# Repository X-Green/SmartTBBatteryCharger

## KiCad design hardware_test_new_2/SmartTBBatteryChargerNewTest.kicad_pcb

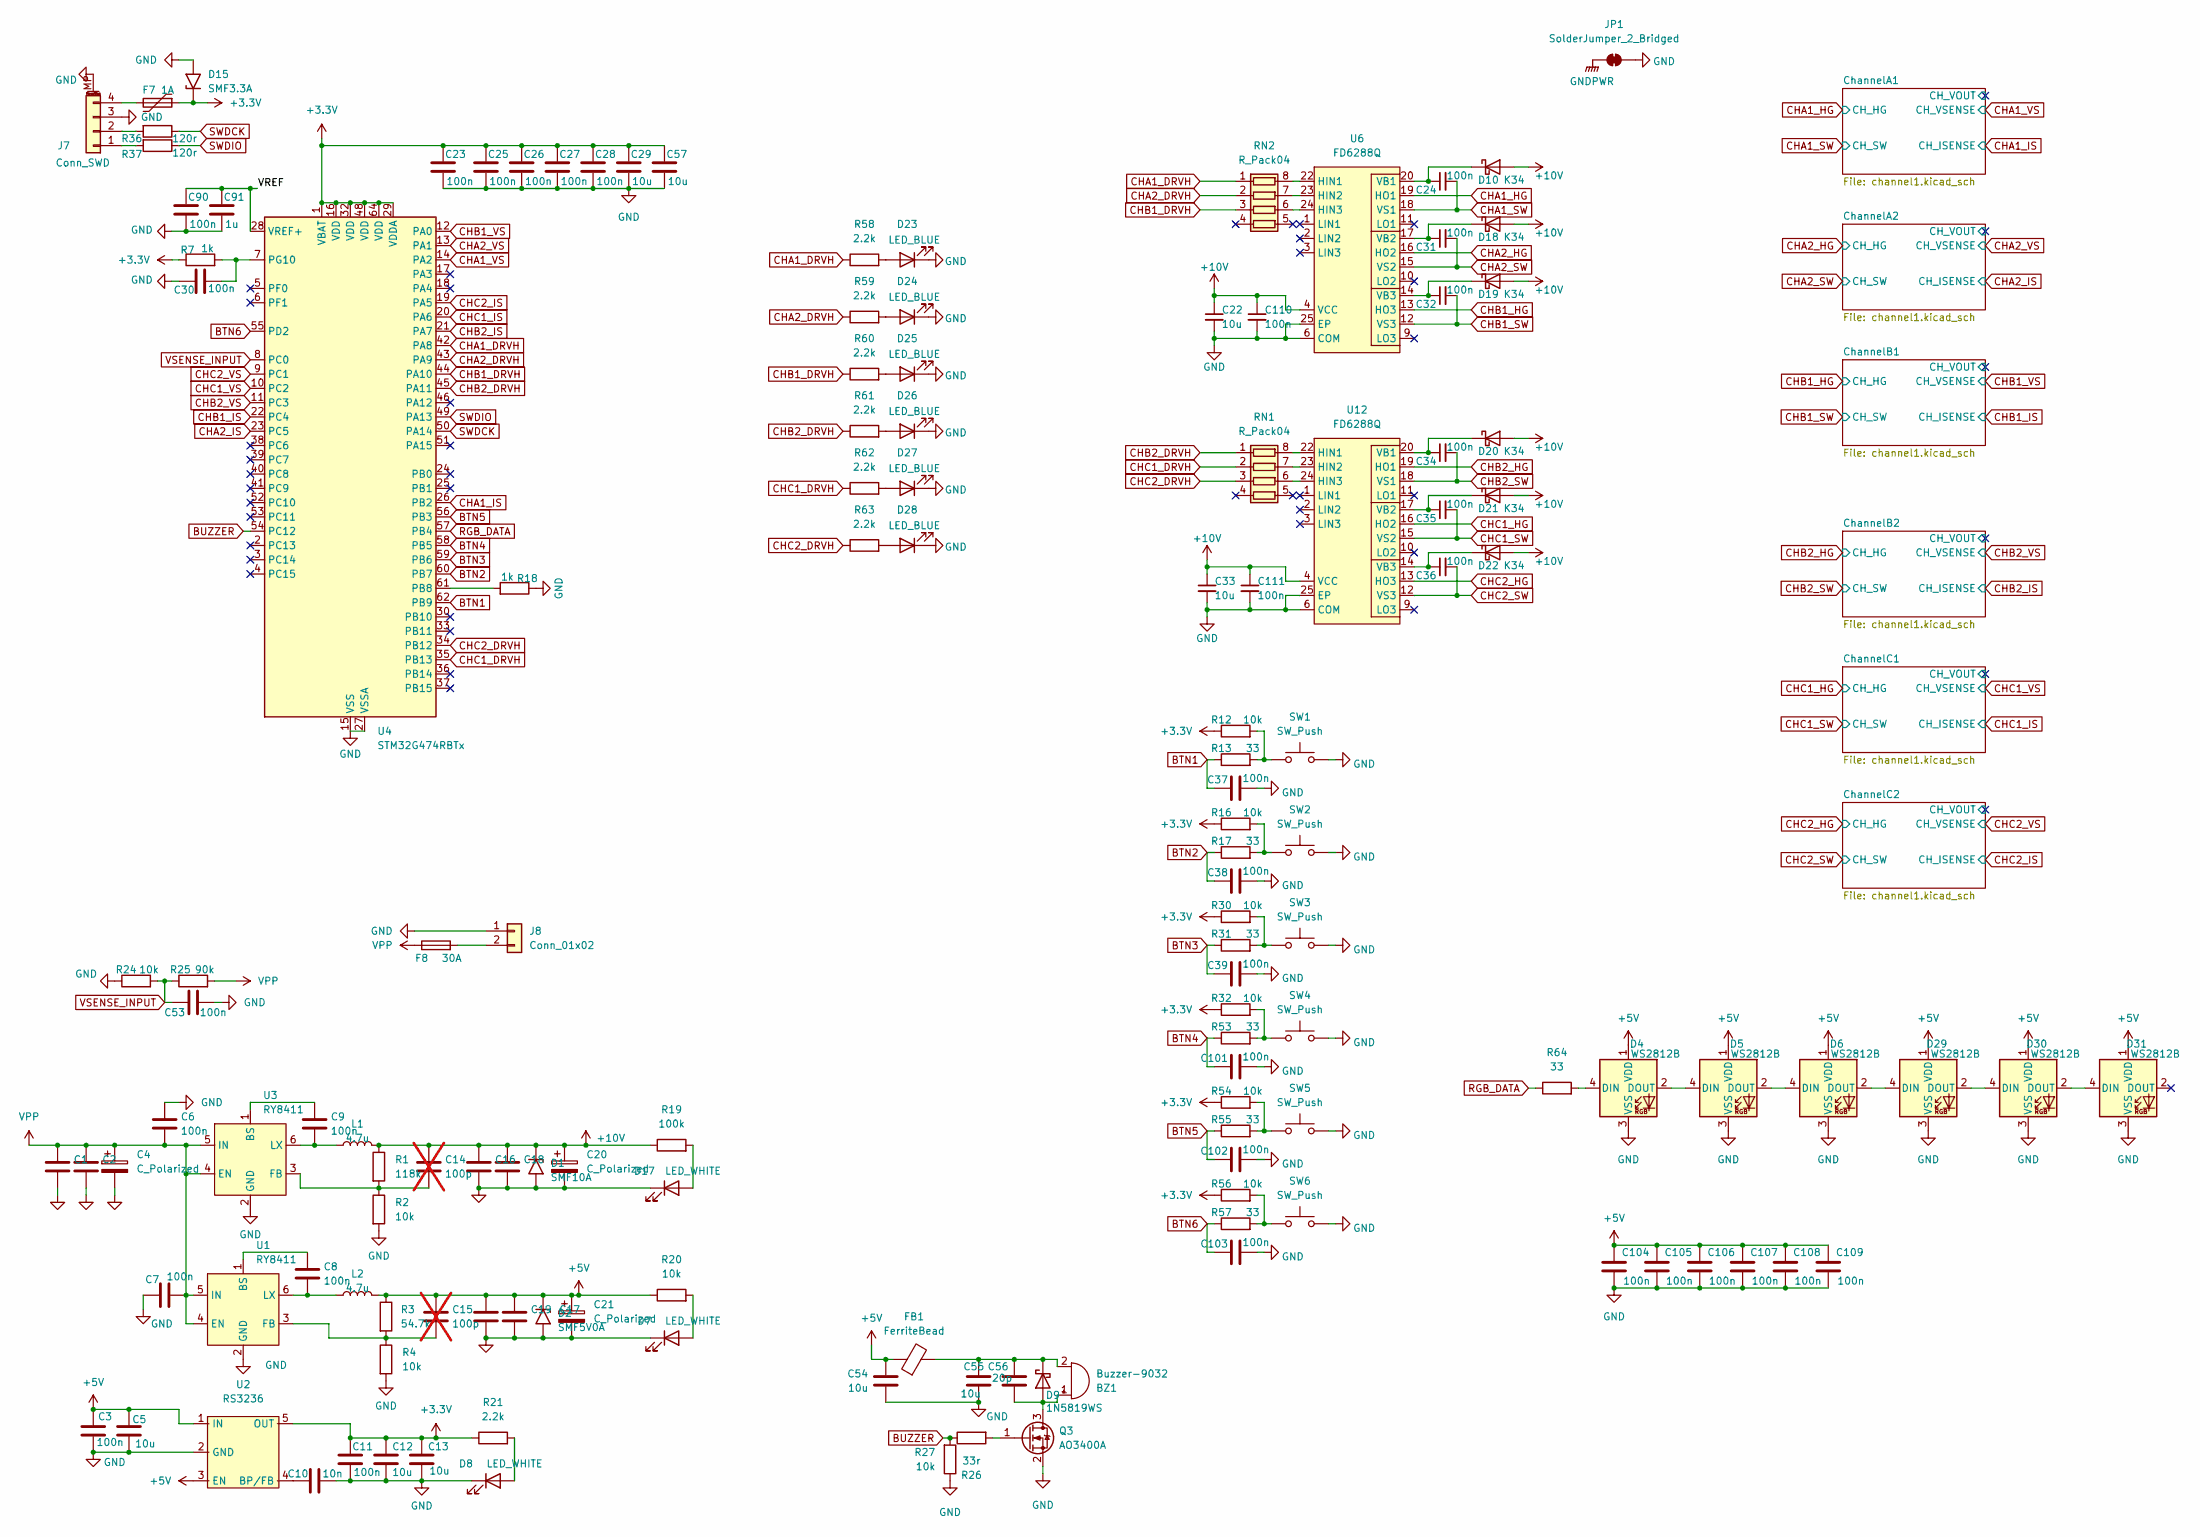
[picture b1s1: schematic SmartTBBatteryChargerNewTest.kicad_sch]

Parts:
BZ1: Buzzer-9032; MLT-9032
C1, C2, C16, C17, C18, C19, C22, C33: 10u; C_1206_3216Metric
C3, C6, C7, C8, C9, C11, C23, C24, C25, C26, C27, C28, C30, C31, C32, C34, C35, C36, C37, C38, C39, C53, C90, C101, C102, C103, C104, C105, C106, C107, C108, C109, C110, C111: 100n; C_0603_1608Metric
C4, C20, C21: C_Polarized; CP_Radial_D6.3mm_P2.50mm
C5, C12, C13, C29, C54, C55, C57: 10u; C_0603_1608Metric
C10: 10n; C_0603_1608Metric
C14, C15: 100p; C_0603_1608Metric; not fitted
C56: 20p; C_0603_1608Metric
C91: 1u; C_0603_1608Metric
D1: SMF10A; D_SMF
D2: SMF5V0A; D_SMF
D4, D5, D6, D29, D30, D31: WS2812B; LED_WS2812B_PLCC4_5.0x5.0mm_P3.2mm
D7, D8, D17: LED_WHITE; LED_0603_1608Metric
D9: 1N5819WS; D_SOD-323_HandSoldering
D10, D18, D19, D20, D21, D22: K34; D_SOD-123F
D15: SMF3.3A; D_SMF
D23, D24, D25, D26, D27, D28: LED_BLUE; LED_0603_1608Metric
F7: 1A; Fuse_1206_3216Metric
F8: 30A; Fuse_1206_3216Metric
FB1: FerriteBead; L_0603_1608Metric
J7: Conn_SWD; Molex_PicoBlade_53261-0471_1x04-1MP_P1.25mm_Horizontal
J8: Conn_01x02; AMASS_XT60-M_1x02_P7.20mm_Vertical
JP1: SolderJumper_2_Bridged; SolderJumper-2_P1.3mm_Bridged_Pad1.0x1.5mm
L1, L2: 4.7u; L_Bourns-SRN4018
Q3: AO3400A; SOT-23
R1: 118k; R_0603_1608Metric
R2, R4, R12, R16, R20, R24, R27, R30, R32, R54, R56: 10k; R_0603_1608Metric
R3: 54.7k; R_0603_1608Metric
R7, R18: 1k; R_0603_1608Metric
R13, R17, R31, R53, R55, R57, R64: 33; R_0603_1608Metric
R19: 100k; R_0603_1608Metric
R21, R58, R59, R60, R61, R62, R63: 2.2k; R_0603_1608Metric
R25: 90k; R_0603_1608Metric
R26: 33r; R_0603_1608Metric
R36, R37: 120r; R_0603_1608Metric
RN1, RN2: R_Pack04; R_Array_Convex_4x0603
SW1, SW2, SW3, SW4, SW5, SW6: SW_Push; SW_SPST_SKQG_WithStem
U1, U3: RY8411; SOT-23-6
U2: RS3236; SOT-23-5
U4: STM32G474RBTx; LQFP-64_10x10mm_P0.5mm
U6, U12: FD6288Q; QFN-24-1EP_4x4mm_P0.5mm_EP2.7x2.7mm

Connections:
+3.3V: C11.1, C12.1, C13.1, C23.2, C25.2, C26.2, C27.2, C28.2, C29.2, C57.2, D15.1 (A1), F7.1, R7.1, R12.1, R16.1, R21.1, R30.1, R32.1, R54.1, R56.1, U2.5 (OUT), U4.1 (VBAT), U4.16 (VDD), U4.29 (VDDA), U4.32 (VDD), U4.48 (VDD), U4.64 (VDD); also elsewhere on the board
+5V: C3.1, C5.1, C15.1, C17.1, C19.1, C21.1, C54.2, C104.2, C105.2, C106.2, C107.2, C108.2, C109.2, D2.1 (A1), D4.1 (VDD), D5.1 (VDD), D6.1 (VDD), D29.1 (VDD), D30.1 (VDD), D31.1 (VDD), FB1.1, L2.2, R3.1, R20.1, U2.1 (IN), U2.3 (EN)
+10V: C14.1, C16.1, C18.1, C20.1, C22.1, C33.1, C110.1, C111.1, D1.1 (A1), D10.2 (A), D18.2 (A), D19.2 (A), D20.2 (A), D21.2 (A), D22.2 (A), L1.2, R1.1, R19.1, U6.4 (VCC), U12.4 (VCC)
/VREF: C90.2, C91.2, U4.28 (VREF+)
BTN1: C37.2, R13.1, U4.62 (PB9)
BTN2: C38.2, R17.1, U4.60 (PB7)
BTN3: C39.2, R31.1, U4.59 (PB6)
BTN4: C101.2, R53.1, U4.58 (PB5)
BTN5: C102.2, R55.1, U4.56 (PB3)
BTN6: C103.2, R57.1, U4.55 (PD2)
BUZZER: R26.1, R27.2, U4.54 (PC12)
CHA1_DRVH: R58.1, RN2.1 (R1.1), U4.42 (PA8)
CHA1_HG: U6.19 (HO1); also elsewhere on the board
CHA1_IS: U4.26 (PB2); also elsewhere on the board
CHA1_SW: C24.2, U6.18 (VS1); also elsewhere on the board
CHA1_VS: U4.14 (PA2); also elsewhere on the board
CHA2_DRVH: R59.1, RN2.2 (R2.1), U4.43 (PA9)
CHA2_HG: U6.16 (HO2); also elsewhere on the board
CHA2_IS: U4.23 (PC5); also elsewhere on the board
CHA2_SW: C31.2, U6.15 (VS2); also elsewhere on the board
CHA2_VS: U4.13 (PA1); also elsewhere on the board
CHB1_DRVH: R60.1, RN2.3 (R3.1), U4.44 (PA10)
CHB1_HG: U6.13 (HO3); also elsewhere on the board
CHB1_IS: U4.22 (PC4); also elsewhere on the board
CHB1_SW: C32.2, U6.12 (VS3); also elsewhere on the board
CHB1_VS: U4.12 (PA0); also elsewhere on the board
CHB2_DRVH: R61.1, RN1.1 (R1.1), U4.45 (PA11)
CHB2_HG: U12.19 (HO1); also elsewhere on the board
CHB2_IS: U4.21 (PA7); also elsewhere on the board
CHB2_SW: C34.2, U12.18 (VS1); also elsewhere on the board
CHB2_VS: U4.11 (PC3); also elsewhere on the board
CHC1_DRVH: R62.1, RN1.2 (R2.1), U4.35 (PB13)
CHC1_HG: U12.16 (HO2); also elsewhere on the board
CHC1_IS: U4.20 (PA6); also elsewhere on the board
CHC1_SW: C35.2, U12.15 (VS2); also elsewhere on the board
CHC1_VS: U4.10 (PC2); also elsewhere on the board
CHC2_DRVH: R63.1, RN1.3 (R3.1), U4.34 (PB12)
CHC2_HG: U12.13 (HO3); also elsewhere on the board
CHC2_IS: U4.19 (PA5); also elsewhere on the board
CHC2_SW: C36.2, U12.12 (VS3); also elsewhere on the board
CHC2_VS: U4.9 (PC1); also elsewhere on the board
GND: C1.2, C2.2, C3.2, C4.2, C5.2, C6.1, C7.2, C10.2, C11.2, C12.2, C13.2, C16.2, C17.2, C18.2, C19.2, C20.2, C21.2, C22.2, C23.1, C25.1, C26.1, C27.1, C28.1, C29.1, C30.2, C33.2, C37.1, C38.1, C39.1, C53.1, C54.1, C55.1, C57.1, C90.1, C91.1, C101.1, C102.1, C103.1, C104.1, C105.1, C106.1, C107.1, C108.1, C109.1, C110.2, C111.2, D1.2 (A2), D2.2 (A2), D4.3 (VSS), D5.3 (VSS), D6.3 (VSS), D7.1 (K), D8.1 (K), D15.2 (A2), D17.1 (K), D23.1 (K), D24.1 (K), D25.1 (K), D26.1 (K), D27.1 (K), D28.1 (K), D29.3 (VSS), D30.3 (VSS), D31.3 (VSS), J7.3, J7.MP (MountPin), J8.1, JP1.2 (B), Q3.2 (S), R2.2, R4.2, R18.1, R24.1, R27.1, SW1.2, SW2.2, SW3.2, SW4.2, SW5.2, SW6.2, U1.2 (GND), U2.2 (GND), U3.2 (GND), U4.15 (VSS), U4.27 (VSSA), U4.31 (VSS), U4.47 (VSS), U4.63 (VSS), U6.6 (COM), U6.25 (EP), U12.6 (COM), U12.25 (EP); also elsewhere on the board
GNDPWR: JP1.1 (A); also elsewhere on the board
unnamed: BZ1.2 (+), C55.2, C56.2, D9.1 (K), FB1.2
unnamed: BZ1.1 (-), C56.1, D9.2 (A), Q3.3 (D)
unnamed: D4.4 (DIN), R64.2
unnamed: D4.2 (DOUT), D5.4 (DIN)
unnamed: D5.2 (DOUT), D6.4 (DIN)
unnamed: D7.2 (A), R20.2
unnamed: D8.2 (A), R21.2
unnamed: C24.1, D10.1 (K), U6.20 (VB1)
unnamed: D17.2 (A), R19.2
unnamed: C31.1, D18.1 (K), U6.17 (VB2)
unnamed: C32.1, D19.1 (K), U6.14 (VB3)
unnamed: C34.1, D20.1 (K), U12.20 (VB1)
unnamed: C35.1, D21.1 (K), U12.17 (VB2)
unnamed: C36.1, D22.1 (K), U12.14 (VB3)
unnamed: D23.2 (A), R58.2
unnamed: D24.2 (A), R59.2
unnamed: D25.2 (A), R60.2
unnamed: D26.2 (A), R61.2
unnamed: D27.2 (A), R62.2
unnamed: D28.2 (A), R63.2
unnamed: D6.2 (DOUT), D29.4 (DIN)
unnamed: D29.2 (DOUT), D30.4 (DIN)
unnamed: D30.2 (DOUT), D31.4 (DIN)
unnamed: J7.1, R37.2
unnamed: J7.2, R36.2
unnamed: F7.2, J7.4
unnamed: F8.2, J8.2
unnamed: Q3.1 (G), R26.2
unnamed: R12.2, R13.2, SW1.1
unnamed: R16.2, R17.2, SW2.1
unnamed: R30.2, R31.2, SW3.1
unnamed: R32.2, R53.2, SW4.1
unnamed: R54.2, R55.2, SW5.1
unnamed: R56.2, R57.2, SW6.1
unnamed: RN1.8 (R1.2), U12.22 (HIN1)
unnamed: RN1.7 (R2.2), U12.23 (HIN2)
unnamed: RN1.6 (R3.2), U12.24 (HIN3)
unnamed: RN2.8 (R1.2), U6.22 (HIN1)
unnamed: RN2.7 (R2.2), U6.23 (HIN2)
unnamed: RN2.6 (R3.2), U6.24 (HIN3)
unnamed: C8.1, U1.1 (BS)
unnamed: C15.2, R3.2, R4.1, U1.3 (FB)
unnamed: C8.2, L2.1, U1.6 (LX)
unnamed: C10.1, U2.4 (BP/FB)
unnamed: C9.1, U3.1 (BS)
unnamed: C14.2, R1.2, R2.1, U3.3 (FB)
unnamed: C9.2, L1.1, U3.6 (LX)
unnamed: R18.2, U4.61 (PB8)
unnamed: C30.1, R7.2, U4.7 (PG10)
RGB_DATA: R64.1, U4.57 (PB4)
SWDCK: R36.1, U4.50 (PA14)
SWDIO: R37.1, U4.49 (PA13)
VPP: C1.1, C2.1, C4.1, C6.2, C7.1, F8.1, R25.2, U1.4 (EN), U1.5 (IN), U3.4 (EN), U3.5 (IN); also elsewhere on the board
VSENSE_INPUT: C53.2, R24.2, R25.1, U4.8 (PC0)

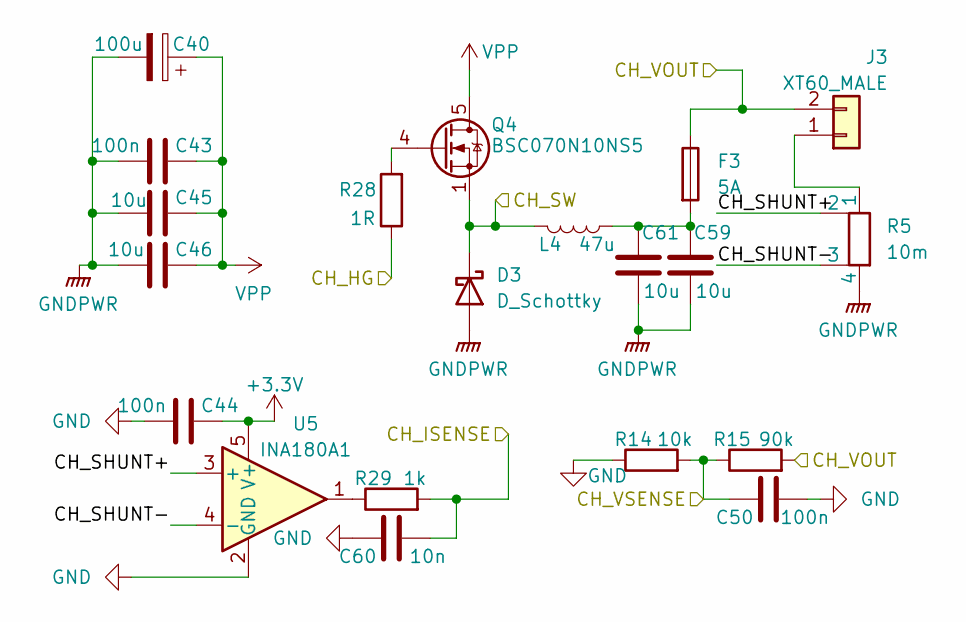
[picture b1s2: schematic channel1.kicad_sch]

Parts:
C40: 100u; CP_Radial_D6.3mm_P2.50mm
C43, C44, C50: 100n; C_0603_1608Metric
C45, C46, C59, C61: 10u; C_1206_3216Metric
C60: 10n; C_0603_1608Metric
D3: D_Schottky; D_PowerDI-5
F3: 5A; Fuse_1206_3216Metric
J3: XT60_MALE; AMASS_XT30U-M_1x02_P5.0mm_Vertical
L4: 47u; L_Coilcraft_MSS1260-XXX
Q4: BSC070N10NS5; TDSON-8-1
R5: 10m; R_Shunt_Vishay_WSK2512_6332Metric_T1.19mm
R14: 10k; R_0603_1608Metric
R15: 90k; R_0603_1608Metric
R28: 1R; R_0603_1608Metric
R29: 1k; R_0603_1608Metric
U5: INA180A1; SOT-23-5

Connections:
+3.3V: C44.1, U5.5 (V+); also elsewhere on the board
/ChannelA1/CH_SHUNT+: R5.2, U5.3 (+)
/ChannelA1/CH_SHUNT-: R5.3, U5.4 (-)
/ChannelA1/CH_VOUT: F3.1, J3.2, R15.2
CHA1_HG: R28.1; also elsewhere on the board
CHA1_IS: C60.1, R29.2; also elsewhere on the board
CHA1_SW: D3.1 (K), L4.1, Q4.1 (S), Q4.2 (S), Q4.3 (S); also elsewhere on the board
CHA1_VS: C50.2, R14.2, R15.1; also elsewhere on the board
GND: C44.2, C50.1, C60.2, R14.1, U5.2 (GND); also elsewhere on the board
GNDPWR: C40.2, C43.2, C45.2, C46.2, C59.2, C61.2, D3.2 (A), R5.4; also elsewhere on the board
unnamed: C59.1, C61.1, F3.2, L4.2
unnamed: J3.1, R5.1
unnamed: Q4.4 (G), R28.2
unnamed: R29.1, U5.1
VPP: C40.1, C43.1, C45.1, C46.1, Q4.5 (D); also elsewhere on the board

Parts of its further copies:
C41, C42, C72, C73, C74: 100u; CP_Radial_D6.3mm_P2.50mm
C47, C51, C52, C58, C67, C71, C75, C76, C77, C84, C85, C86, C98, C99, C100: 100n; C_0603_1608Metric
C48, C49, C63, C64, C65, C66, C69, C70, C78, C79, C80, C81, C82, C83, C92, C93, C94, C95, C96, C97: 10u; C_1206_3216Metric
C62, C68, C87, C88, C89: 10n; C_0603_1608Metric
D11, D12, D13, D14, D16: D_Schottky; D_PowerDI-5
F4, F5, F6, F9, F10: 5A; Fuse_1206_3216Metric
J4, J5, J6, J9, J10: XT60_MALE; AMASS_XT30U-M_1x02_P5.0mm_Vertical
L5, L6, L7, L8, L9: 47u; L_Coilcraft_MSS1260-XXX
Q5, Q6, Q7, Q8, Q9: BSC070N10NS5; TDSON-8-1
R6, R8, R9, R10, R11: 10m; R_Shunt_Vishay_WSK2512_6332Metric_T1.19mm
R22, R39, R47, R48, R49: 10k; R_0603_1608Metric
R23, R40, R50, R51, R52: 90k; R_0603_1608Metric
R33, R35, R41, R42, R43: 1R; R_0603_1608Metric
R34, R38, R44, R45, R46: 1k; R_0603_1608Metric
U7, U8, U9, U10, U11: INA180A1; SOT-23-5

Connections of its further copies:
+3.3V: C51.1, C67.1, C84.1, C85.1, C86.1, U7.5 (V+), U8.5 (V+), U9.5 (V+), U10.5 (V+), U11.5 (V+); also elsewhere on the board
/ChannelA2/CH_SHUNT+: R6.2, U7.3 (+)
/ChannelA2/CH_SHUNT-: R6.3, U7.4 (-)
/ChannelA2/CH_VOUT: F4.1, J4.2, R23.2
/ChannelB1/CH_SHUNT+: R8.2, U8.3 (+)
/ChannelB1/CH_SHUNT-: R8.3, U8.4 (-)
/ChannelB1/CH_VOUT: F5.1, J5.2, R40.2
/ChannelB2/CH_SHUNT+: R9.2, U9.3 (+)
/ChannelB2/CH_SHUNT-: R9.3, U9.4 (-)
/ChannelB2/CH_VOUT: F6.1, J6.2, R50.2
/ChannelC1/CH_SHUNT+: R10.2, U10.3 (+)
/ChannelC1/CH_SHUNT-: R10.3, U10.4 (-)
/ChannelC1/CH_VOUT: F9.1, J9.2, R51.2
/ChannelC2/CH_SHUNT+: R11.2, U11.3 (+)
/ChannelC2/CH_SHUNT-: R11.3, U11.4 (-)
/ChannelC2/CH_VOUT: F10.1, J10.2, R52.2
CHA2_HG: R33.1; also elsewhere on the board
CHA2_IS: C62.1, R34.2; also elsewhere on the board
CHA2_SW: D11.1 (K), L5.1, Q5.1 (S), Q5.2 (S), Q5.3 (S); also elsewhere on the board
CHA2_VS: C52.2, R22.2, R23.1; also elsewhere on the board
CHB1_HG: R35.1; also elsewhere on the board
CHB1_IS: C68.1, R38.2; also elsewhere on the board
CHB1_SW: D12.1 (K), L6.1, Q6.1 (S), Q6.2 (S), Q6.3 (S); also elsewhere on the board
CHB1_VS: C71.2, R39.2, R40.1; also elsewhere on the board
CHB2_HG: R41.1; also elsewhere on the board
CHB2_IS: C87.1, R44.2; also elsewhere on the board
CHB2_SW: D13.1 (K), L7.1, Q7.1 (S), Q7.2 (S), Q7.3 (S); also elsewhere on the board
CHB2_VS: C98.2, R47.2, R50.1; also elsewhere on the board
CHC1_HG: R42.1; also elsewhere on the board
CHC1_IS: C88.1, R45.2; also elsewhere on the board
CHC1_SW: D14.1 (K), L8.1, Q8.1 (S), Q8.2 (S), Q8.3 (S); also elsewhere on the board
CHC1_VS: C99.2, R48.2, R51.1; also elsewhere on the board
CHC2_HG: R43.1; also elsewhere on the board
CHC2_IS: C89.1, R46.2; also elsewhere on the board
CHC2_SW: D16.1 (K), L9.1, Q9.1 (S), Q9.2 (S), Q9.3 (S); also elsewhere on the board
CHC2_VS: C100.2, R49.2, R52.1; also elsewhere on the board
GND: C51.2, C52.1, C62.2, C67.2, C68.2, C71.1, C84.2, C85.2, C86.2, C87.2, C88.2, C89.2, C98.1, C99.1, C100.1, R22.1, R39.1, R47.1, R48.1, R49.1, U7.2 (GND), U8.2 (GND), U9.2 (GND), U10.2 (GND), U11.2 (GND); also elsewhere on the board
GNDPWR: C41.2, C42.2, C47.2, C48.2, C49.2, C58.2, C63.2, C64.2, C65.2, C66.2, C69.2, C70.2, C72.2, C73.2, C74.2, C75.2, C76.2, C77.2, C78.2, C79.2, C80.2, C81.2, C82.2, C83.2, C92.2, C93.2, C94.2, C95.2, C96.2, C97.2, D11.2 (A), D12.2 (A), D13.2 (A), D14.2 (A), D16.2 (A), R6.4, R8.4, R9.4, R10.4, R11.4; also elsewhere on the board
unnamed: C63.1, C64.1, F4.2, L5.2
unnamed: C69.1, C70.1, F5.2, L6.2
unnamed: C92.1, C97.1, F10.2, L9.2
unnamed: C93.1, C96.1, F9.2, L8.2
unnamed: C94.1, C95.1, F6.2, L7.2
unnamed: J4.1, R6.1
unnamed: J5.1, R8.1
unnamed: J6.1, R9.1
unnamed: J9.1, R10.1
unnamed: J10.1, R11.1
unnamed: Q5.4 (G), R33.2
unnamed: Q6.4 (G), R35.2
unnamed: Q7.4 (G), R41.2
unnamed: Q8.4 (G), R42.2
unnamed: Q9.4 (G), R43.2
unnamed: R34.1, U7.1
unnamed: R38.1, U8.1
unnamed: R44.1, U9.1
unnamed: R45.1, U10.1
unnamed: R46.1, U11.1
VPP: C41.1, C42.1, C47.1, C48.1, C49.1, C58.1, C65.1, C66.1, C72.1, C73.1, C74.1, C75.1, C76.1, C77.1, C78.1, C79.1, C80.1, C81.1, C82.1, C83.1, Q5.5 (D), Q6.5 (D), Q7.5 (D), Q8.5 (D), Q9.5 (D); also elsewhere on the board

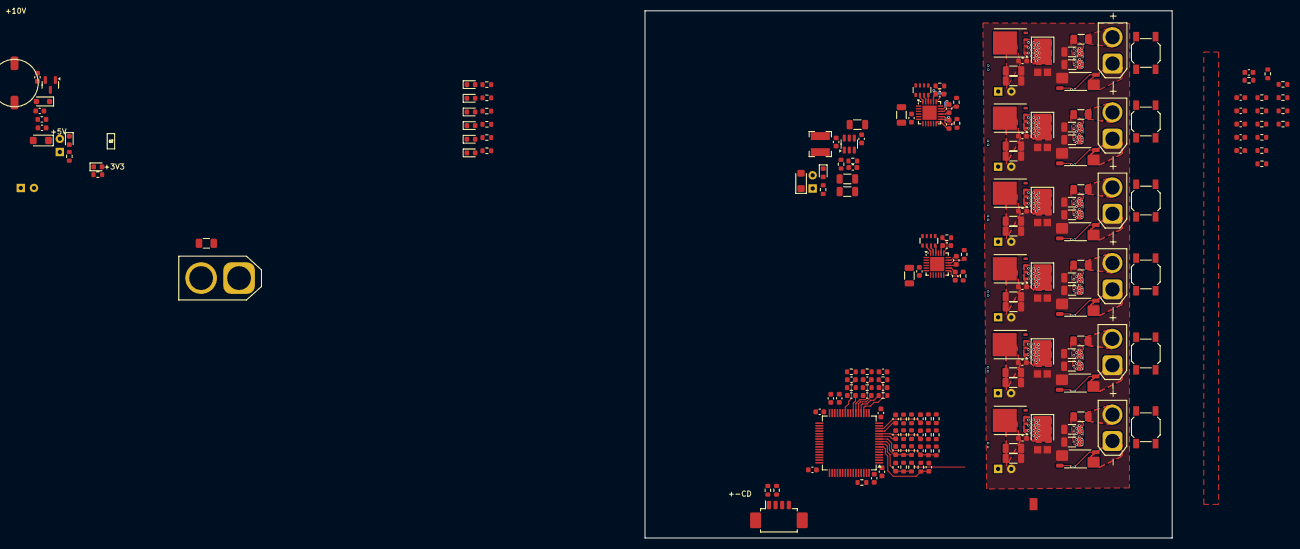
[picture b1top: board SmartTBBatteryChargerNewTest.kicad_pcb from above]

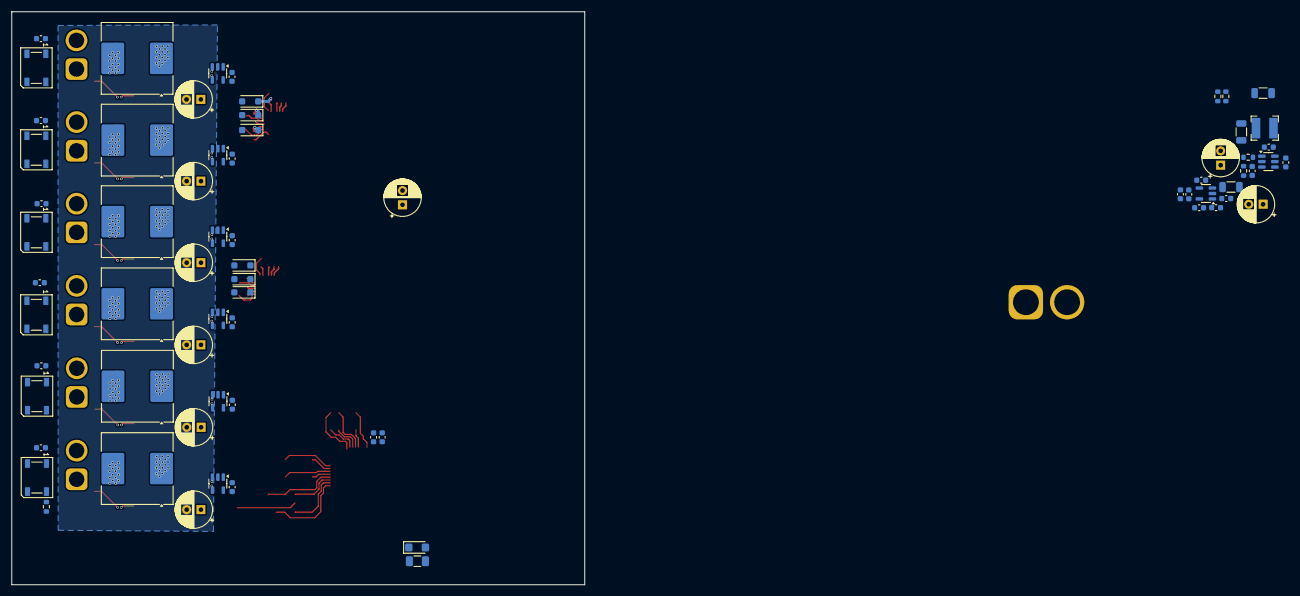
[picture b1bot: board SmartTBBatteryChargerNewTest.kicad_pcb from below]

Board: 4 copper layers, 100.0 x 100.0 mm, 260 parts (69 on the bottom side), 139 nets.

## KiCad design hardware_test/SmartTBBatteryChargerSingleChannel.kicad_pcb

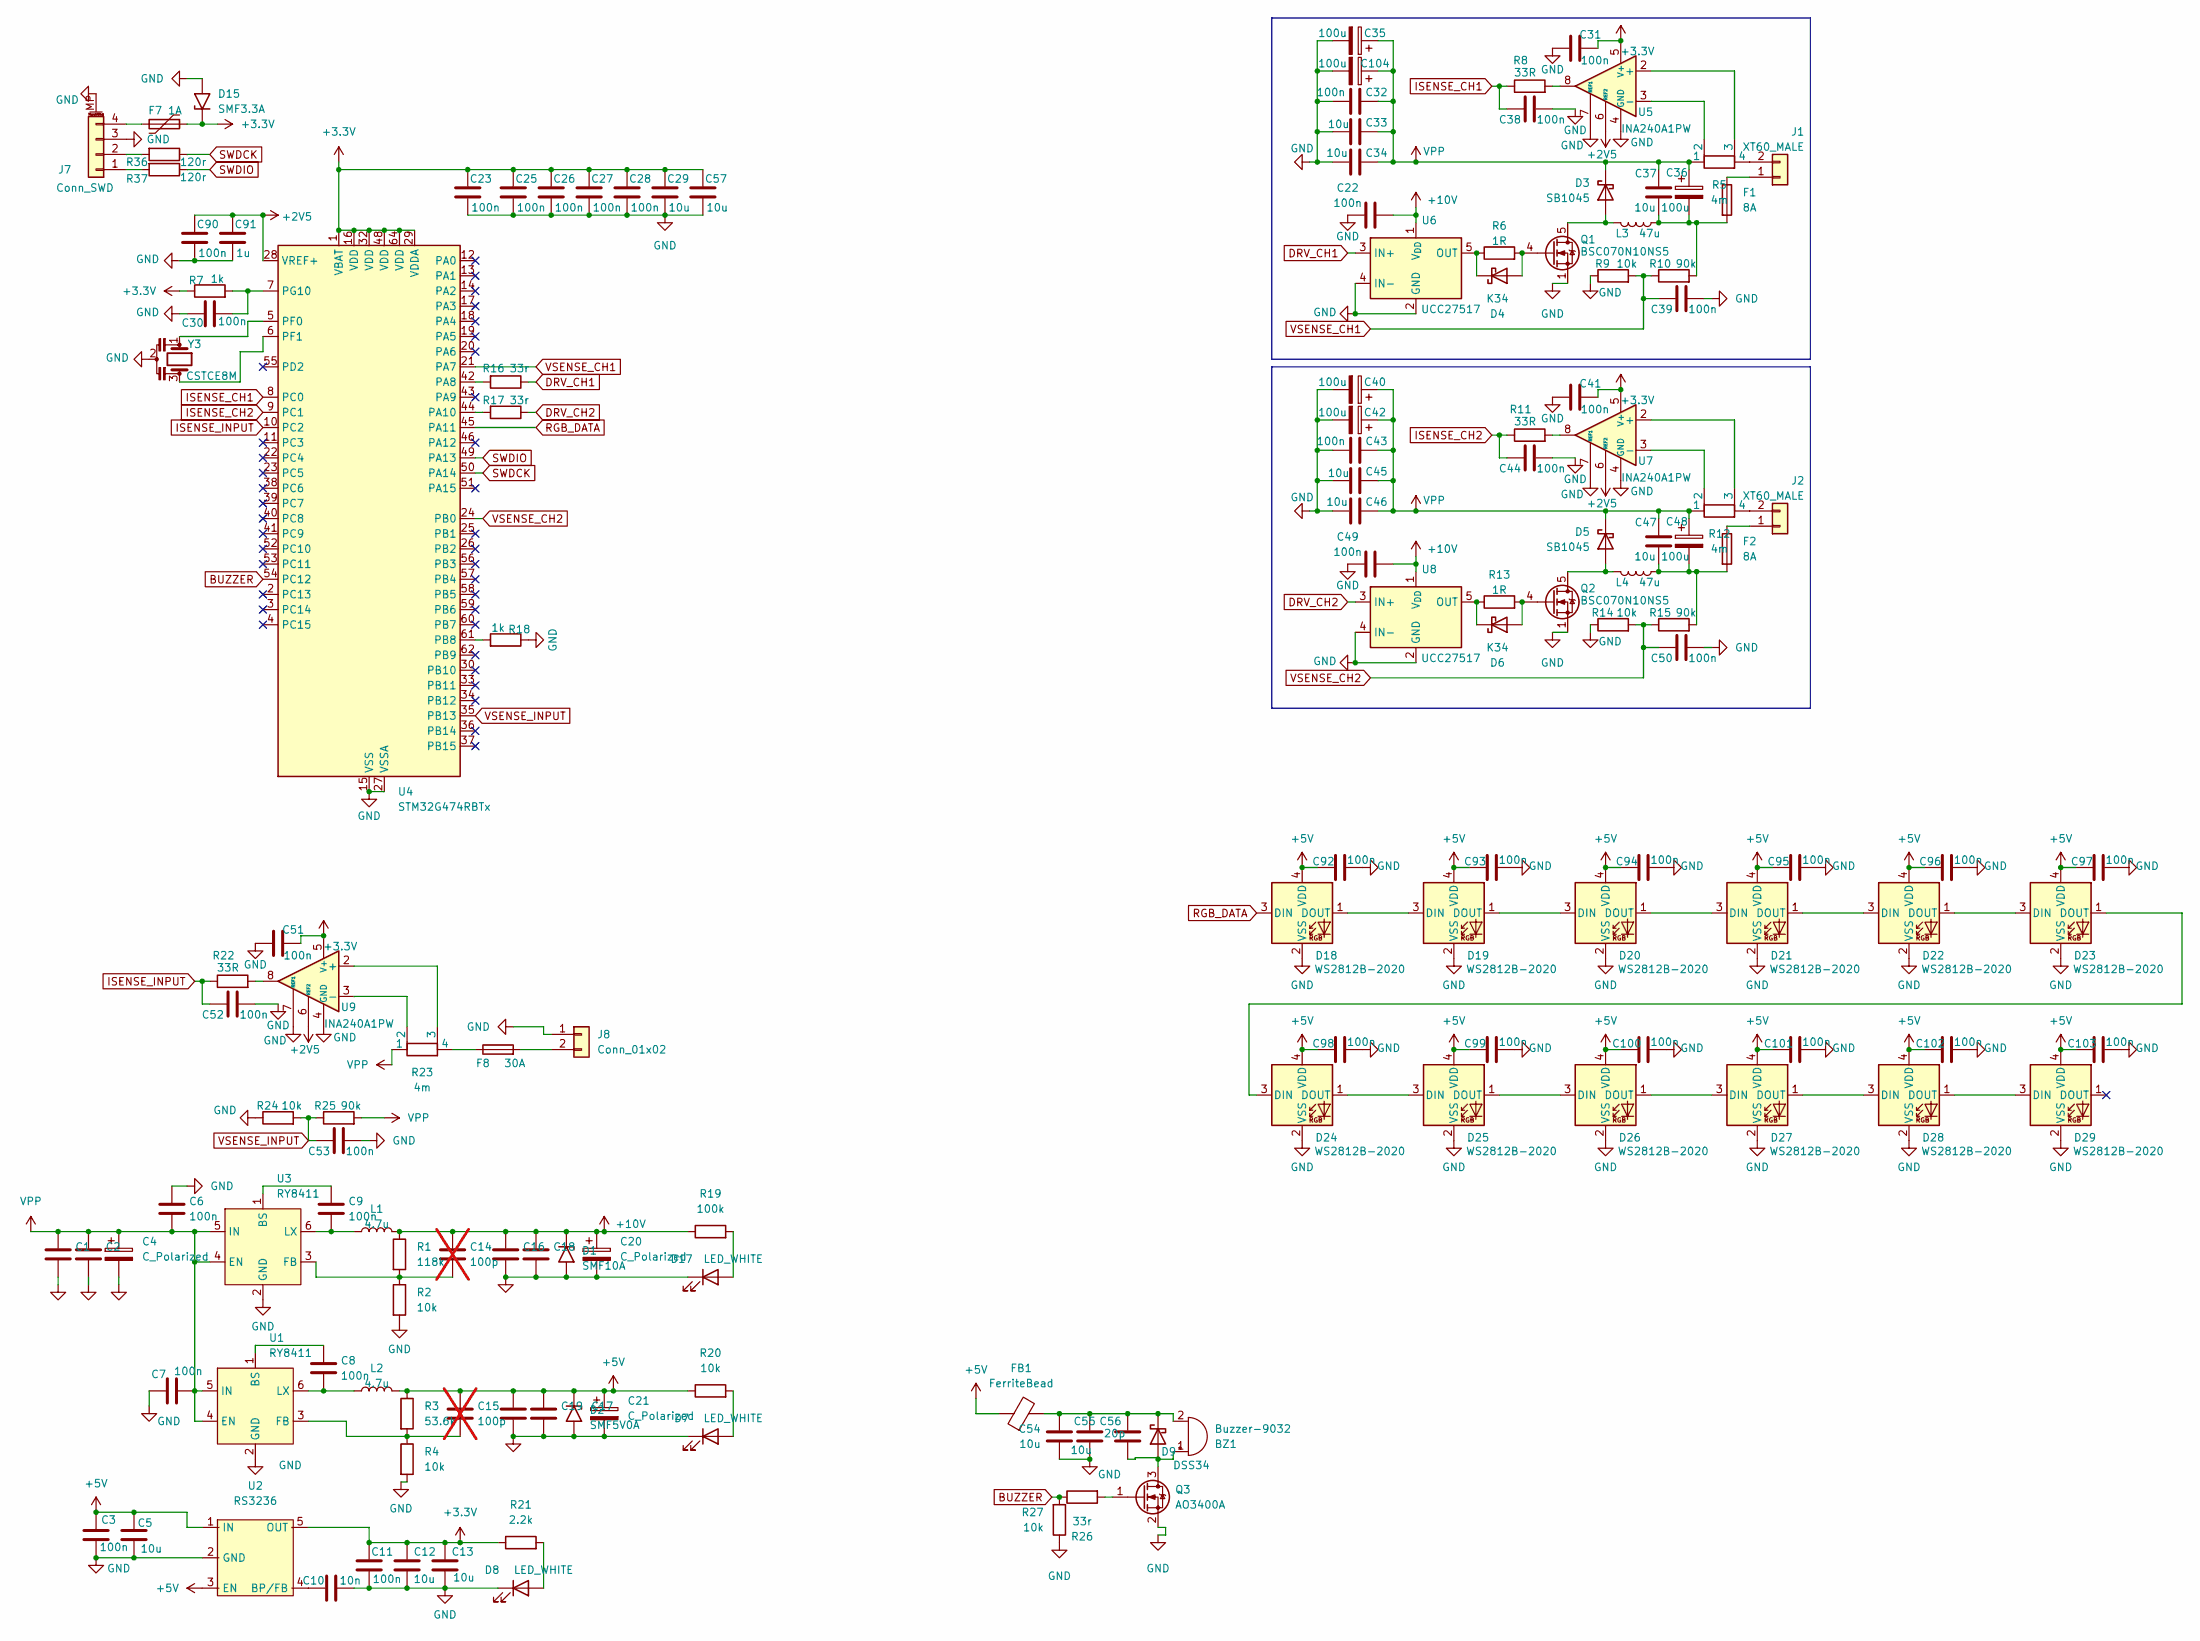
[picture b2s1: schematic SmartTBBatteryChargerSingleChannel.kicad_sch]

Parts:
BZ1: Buzzer-9032; MLT-9032
C1, C2, C16, C17, C18, C19, C33, C34, C37, C45, C46, C47: 10u; C_1206_3216Metric
C3, C6, C7, C8, C9, C11, C22, C23, C25, C26, C27, C28, C30, C31, C32, C38, C39, C41, C43, C44, C49, C50, C51, C52, C53, C90, C92, C93, C94, C95, C96, C97, C98, C99, C100, C101, C102, C103: 100n; C_0603_1608Metric
C4, C20, C21: C_Polarized; CP_Radial_D6.3mm_P2.50mm
C5, C12, C13, C29, C54, C55, C57: 10u; C_0603_1608Metric
C10: 10n; C_0603_1608Metric
C14, C15: 100p; C_0603_1608Metric; not fitted
C35, C36, C40, C42, C48, C104: 100u; CP_Radial_D6.3mm_P2.50mm
C56: 20p; C_0603_1608Metric
C91: 1u; C_0603_1608Metric
D1: SMF10A; D_SMF
D2: SMF5V0A; D_SMF
D3, D5: SB1045; D_PowerDI-5
D4, D6: K34; D_SOD-123F
D7, D8, D17: LED_WHITE; LED_0603_1608Metric
D9: DSS34; D_SMF
D15: SMF3.3A; D_SMF
D18, D19, D20, D21, D22, D23, D24, D25, D26, D27, D28, D29: WS2812B-2020; LED_WS2812B-2020_PLCC4_2.0x2.0mm
F1, F2: 8A; Fuse_1206_3216Metric
F7: 1A; Fuse_1206_3216Metric
F8: 30A; Fuse_1206_3216Metric
FB1: FerriteBead; L_0603_1608Metric
J1, J2: XT60_MALE; AMASS_XT60-M_1x02_P7.20mm_Vertical
J7: Conn_SWD; Molex_PicoBlade_53261-0471_1x04-1MP_P1.25mm_Horizontal
J8: Conn_01x02; AMASS_XT30U-M_1x02_P5.0mm_Vertical
L1, L2: 4.7u; L_Bourns-SRN4018
L3, L4: 47u; L_Coilcraft_MSS1260-XXX
Q1, Q2: BSC070N10NS5; TDSON-8-1
Q3: AO3400A; SOT-23
R1: 118k; R_0603_1608Metric
R2, R4, R9, R14, R20, R24, R27: 10k; R_0603_1608Metric
R3: 53.6k; R_0603_1608Metric
R5, R12, R23: 4m; R_Shunt_Vishay_WSK2512_6332Metric_T1.19mm
R6, R13: 1R; R_0603_1608Metric
R7, R18: 1k; R_0603_1608Metric
R8, R11, R22: 33R; R_0603_1608Metric
R10, R15, R25: 90k; R_0603_1608Metric
R16, R17, R26: 33r; R_0603_1608Metric
R19: 100k; R_0603_1608Metric
R21: 2.2k; R_0603_1608Metric
R36, R37: 120r; R_0603_1608Metric
U1, U3: RY8411; SOT-23-6
U2: RS3236; SOT-23-5
U4: STM32G474RBTx; LQFP-64_10x10mm_P0.5mm
U5, U7, U9: INA240A1PW; TSSOP-8_4.4x3mm_P0.65mm
U6, U8: UCC27517; SOT-23-5
Y3: CSTCE8M; Resonator_SMD_Murata_CSTxExxV-3Pin_3.0x1.1mm_HandSoldering

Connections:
+2V5: C90.2, C91.2, U4.28 (VREF+), U5.6 (REF2), U7.6 (REF2), U9.6 (REF2)
+3.3V: C11.1, C12.1, C13.1, C23.2, C25.2, C26.2, C27.2, C28.2, C29.2, C31.1, C41.1, C51.1, C57.2, D15.1 (A1), F7.1, R7.1, R21.1, U2.5 (OUT), U4.1 (VBAT), U4.16 (VDD), U4.29 (VDDA), U4.32 (VDD), U4.48 (VDD), U4.64 (VDD), U5.5 (V+), U7.5 (V+), U9.5 (V+)
+5V: C3.1, C5.1, C15.1, C17.1, C19.1, C21.1, C92.2, C93.2, C94.2, C95.2, C96.2, C97.2, C98.2, C99.2, C100.2, C101.2, C102.2, C103.2, D2.1 (A1), D18.4 (VDD), D19.4 (VDD), D20.4 (VDD), D21.4 (VDD), D22.4 (VDD), D23.4 (VDD), D24.4 (VDD), D25.4 (VDD), D26.4 (VDD), D27.4 (VDD), D28.4 (VDD), D29.4 (VDD), FB1.1, L2.2, R3.1, R20.1, U2.1 (IN), U2.3 (EN)
+10V: C14.1, C16.1, C18.1, C20.1, C22.1, C49.1, D1.1 (A1), L1.2, R1.1, R19.1, U6.1 (V_{DD}), U8.1 (V_{DD})
BUZZER: R26.1, R27.2, U4.54 (PC12)
DRV_CH1: R16.1, U6.3 (IN+)
DRV_CH2: R17.1, U8.3 (IN+)
GND: C1.2, C2.2, C3.2, C4.2, C5.2, C6.1, C7.2, C10.2, C11.2, C12.2, C13.2, C16.2, C17.2, C18.2, C19.2, C20.2, C21.2, C22.2, C23.1, C25.1, C26.1, C27.1, C28.1, C29.1, C30.2, C31.2, C32.2, C33.2, C34.2, C35.2, C38.1, C39.1, C40.2, C41.2, C42.2, C43.2, C44.1, C45.2, C46.2, C49.2, C50.1, C51.2, C52.1, C53.1, C54.1, C55.1, C57.1, C90.1, C91.1, C92.1, C93.1, C94.1, C95.1, C96.1, C97.1, C98.1, C99.1, C100.1, C101.1, C102.1, C103.1, C104.2, D1.2 (A2), D2.2 (A2), D7.1 (K), D8.1 (K), D15.2 (A2), D17.1 (K), D18.2 (VSS), D19.2 (VSS), D20.2 (VSS), D21.2 (VSS), D22.2 (VSS), D23.2 (VSS), D24.2 (VSS), D25.2 (VSS), D26.2 (VSS), D27.2 (VSS), D28.2 (VSS), D29.2 (VSS), J7.3, J7.MP (MountPin), J8.1, Q1.1 (S), Q1.2 (S), Q1.3 (S), Q2.1 (S), Q2.2 (S), Q2.3 (S), Q3.2 (S), R2.2, R4.2, R9.1, R14.1, R18.1, R24.1, R27.1, U1.2 (GND), U2.2 (GND), U3.2 (GND), U4.15 (VSS), U4.27 (VSSA), U4.31 (VSS), U4.47 (VSS), U4.63 (VSS), U5.1 (GND), U5.4 (GND), U5.7 (REF1), U6.2 (GND), U6.4 (IN-), U7.1 (GND), U7.4 (GND), U7.7 (REF1), U8.2 (GND), U8.4 (IN-), U9.1 (GND), U9.4 (GND), U9.7 (REF1), Y3.2
ISENSE_CH1: C38.2, R8.1, U4.8 (PC0)
ISENSE_CH2: C44.2, R11.1, U4.9 (PC1)
ISENSE_INPUT: C52.2, R22.1, U4.10 (PC2)
unnamed: BZ1.2 (+), C54.2, C55.2, C56.2, D9.1 (K), FB1.2
unnamed: BZ1.1 (-), C56.1, D9.2 (A), Q3.3 (D)
unnamed: C36.2, C37.2, F1.2, L3.2, R10.2
unnamed: C47.2, C48.2, F2.2, L4.2, R15.2
unnamed: D3.2 (A), L3.1, Q1.5 (D)
unnamed: D4.2 (A), Q1.4 (G), R6.2
unnamed: D4.1 (K), R6.1, U6.5 (OUT)
unnamed: D5.2 (A), L4.1, Q2.5 (D)
unnamed: D6.2 (A), Q2.4 (G), R13.2
unnamed: D6.1 (K), R13.1, U8.5 (OUT)
unnamed: D7.2 (A), R20.2
unnamed: D8.2 (A), R21.2
unnamed: D17.2 (A), R19.2
unnamed: D18.1 (DOUT), D19.3 (DIN)
unnamed: D19.1 (DOUT), D20.3 (DIN)
unnamed: D20.1 (DOUT), D21.3 (DIN)
unnamed: D21.1 (DOUT), D22.3 (DIN)
unnamed: D22.1 (DOUT), D23.3 (DIN)
unnamed: D23.1 (DOUT), D24.3 (DIN)
unnamed: D24.1 (DOUT), D25.3 (DIN)
unnamed: D25.1 (DOUT), D26.3 (DIN)
unnamed: D26.1 (DOUT), D27.3 (DIN)
unnamed: D27.1 (DOUT), D28.3 (DIN)
unnamed: D28.1 (DOUT), D29.3 (DIN)
unnamed: F8.1, R23.4
unnamed: F1.1, J1.1
unnamed: J1.2, R5.4
unnamed: F2.1, J2.1
unnamed: J2.2, R12.4
unnamed: J7.1, R37.2
unnamed: J7.2, R36.2
unnamed: F7.2, J7.4
unnamed: F8.2, J8.2
unnamed: Q3.1 (G), R26.2
unnamed: R8.2, U5.8
unnamed: R11.2, U7.8
unnamed: R22.2, U9.8
unnamed: C8.1, U1.1 (BS)
unnamed: C15.2, R3.2, R4.1, U1.3 (FB)
unnamed: C8.2, L2.1, U1.6 (LX)
unnamed: C10.1, U2.4 (BP/FB)
unnamed: C9.1, U3.1 (BS)
unnamed: C14.2, R1.2, R2.1, U3.3 (FB)
unnamed: C9.2, L1.1, U3.6 (LX)
unnamed: R16.2, U4.42 (PA8)
unnamed: R17.2, U4.44 (PA10)
unnamed: R18.2, U4.61 (PB8)
unnamed: U4.5 (PF0), Y3.1
unnamed: U4.6 (PF1), Y3.3
unnamed: C30.1, R7.2, U4.7 (PG10)
unnamed: R5.3, U5.2 (+)
unnamed: R5.2, U5.3 (-)
unnamed: R12.3, U7.2 (+)
unnamed: R12.2, U7.3 (-)
unnamed: R23.3, U9.2 (+)
unnamed: R23.2, U9.3 (-)
RGB_DATA: D18.3 (DIN), U4.45 (PA11)
SWDCK: R36.1, U4.50 (PA14)
SWDIO: R37.1, U4.49 (PA13)
VPP: C1.1, C2.1, C4.1, C6.2, C7.1, C32.1, C33.1, C34.1, C35.1, C36.1, C37.1, C40.1, C42.1, C43.1, C45.1, C46.1, C47.1, C48.1, C104.1, D3.1 (K), D5.1 (K), R5.1, R12.1, R23.1, R25.2, U1.4 (EN), U1.5 (IN), U3.4 (EN), U3.5 (IN)
VSENSE_CH1: C39.2, R9.2, R10.1, U4.21 (PA7)
VSENSE_CH2: C50.2, R14.2, R15.1, U4.24 (PB0)
VSENSE_INPUT: C53.2, R24.2, R25.1, U4.35 (PB13)

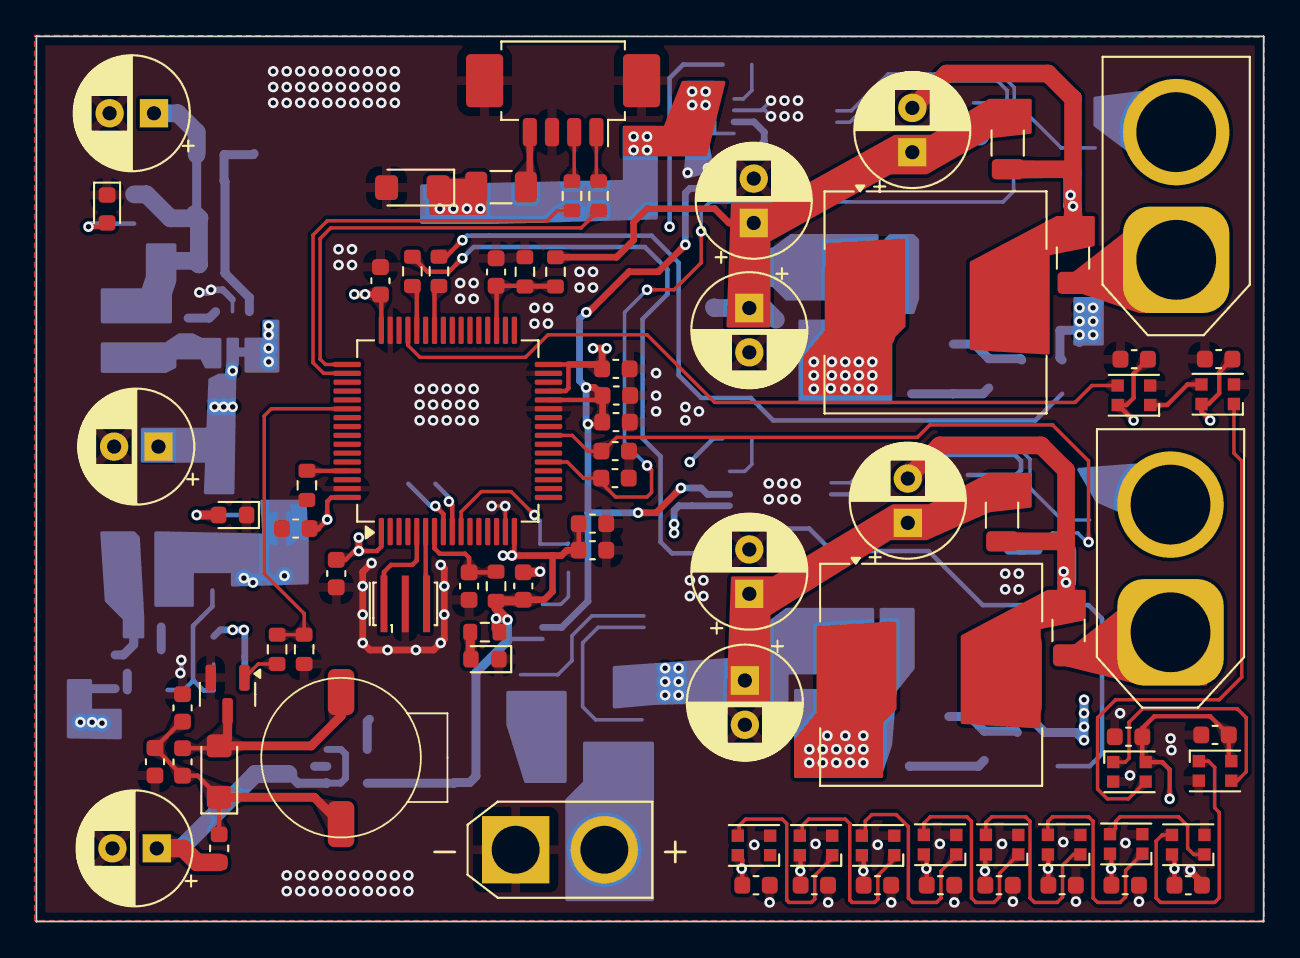
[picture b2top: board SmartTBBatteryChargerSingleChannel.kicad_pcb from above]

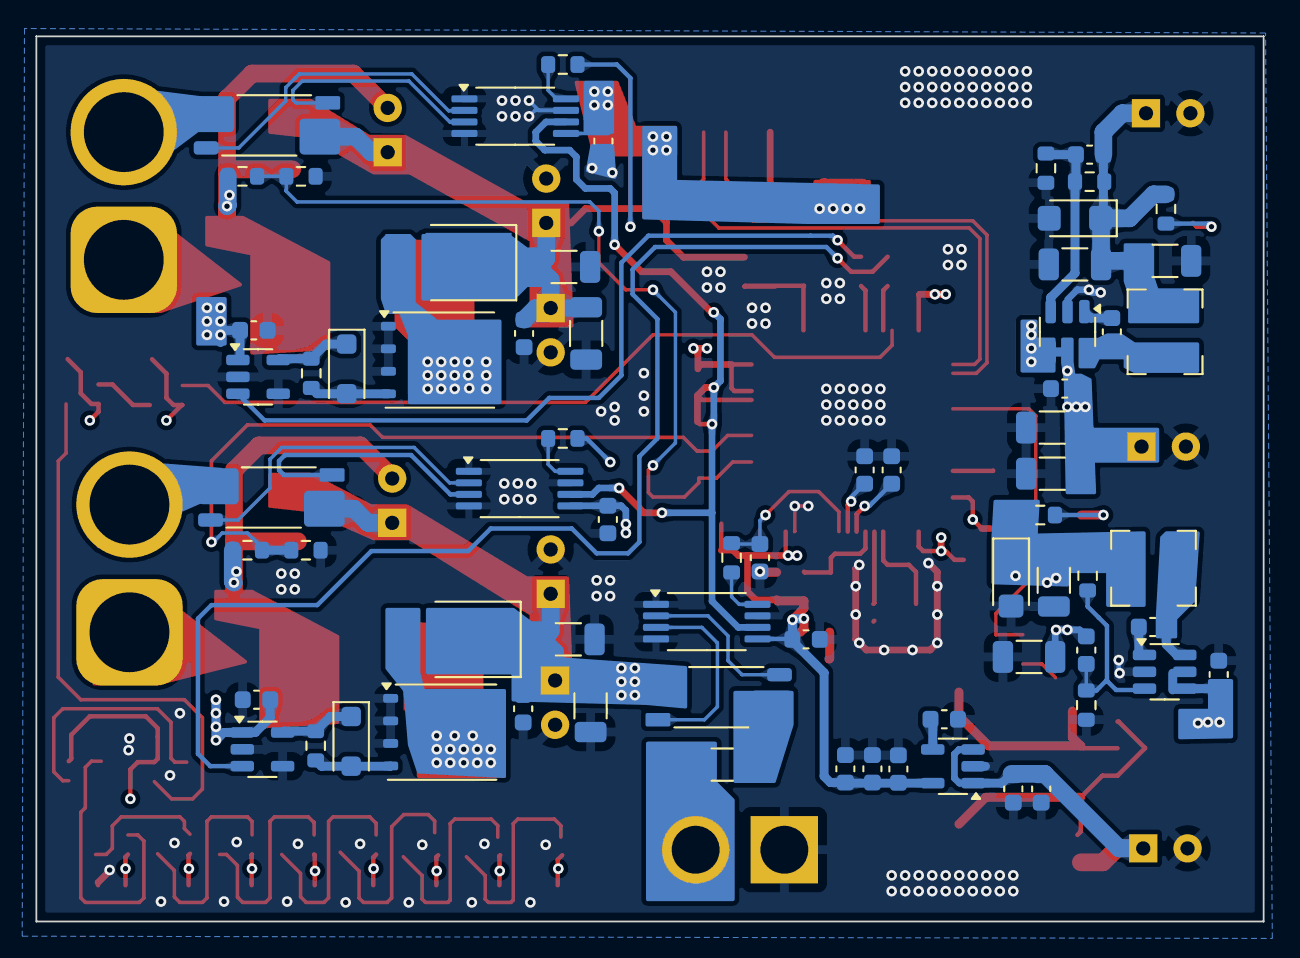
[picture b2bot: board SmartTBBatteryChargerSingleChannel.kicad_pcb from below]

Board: 4 copper layers, 69.2 x 49.9 mm, 150 parts (69 on the bottom side), 74 nets.
